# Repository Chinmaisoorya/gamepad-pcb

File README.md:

# Custom USB Gamepad PCB

A 2-layer PCB gamepad built around the ATmega32U4 microcontroller. It enumerates as a standard Xbox 360 controller on Windows via XInput — no drivers needed.

## Features

- Native USB 2.0 HID via ATmega32U4
- Dual analog joysticks (5-pin headers)
- 4 tactile buttons (A / B / X / Y)
- 16MHz external crystal for USB timing
- 2-layer PCB — hand-routed
- USB-C connector

## Preview

## Tech Stack

| Layer | Tool |
|-------|------|
| Schematic | KiCad 8 |
| PCB Layout | KiCad 8 |
| Firmware | Arduino + XInput library |
| Manufacturing | JLCPCB-compatible Gerbers |

## Repository Structure
gamepad-pcb/
├── hardware/ KiCad project + Gerbers
├── firmware/ Arduino XInput code
├── images/ Renders and screenshots
└── README.md

## Hardware Details

- **MCU:** ATmega32U4-AU (QFN-44)
- **Crystal:** 16MHz HC49
- **USB:** USB-C receptacle (USB 2.0)
- **Joysticks:** 5-pin headers × 2
- **Buttons:** 6mm tactile push buttons × 4
- **PCB:** 2-layer, 1.6mm FR4

## Building the Firmware

1. Install the [Arduino XInput library](https://github.com/dmadison/ArduinoXInput).
2. Open `firmware/gamepad.ino`.
3. Select **Arduino Leonardo** as the board (ATmega32U4).
4. Upload via USB.

The gamepad will appear in Windows as **"Xbox 360 Controller"**.

## Manufacturing

Gerbers are in `hardware/gamepad_gerbers.zip`. Upload directly to JLCPCB or PCBWay.

## License

MIT — free to use, modify, and build.

## Author

Chinmai soorya P — [www.linkedin.com/in/chinmai-soorya-p-52184941a]

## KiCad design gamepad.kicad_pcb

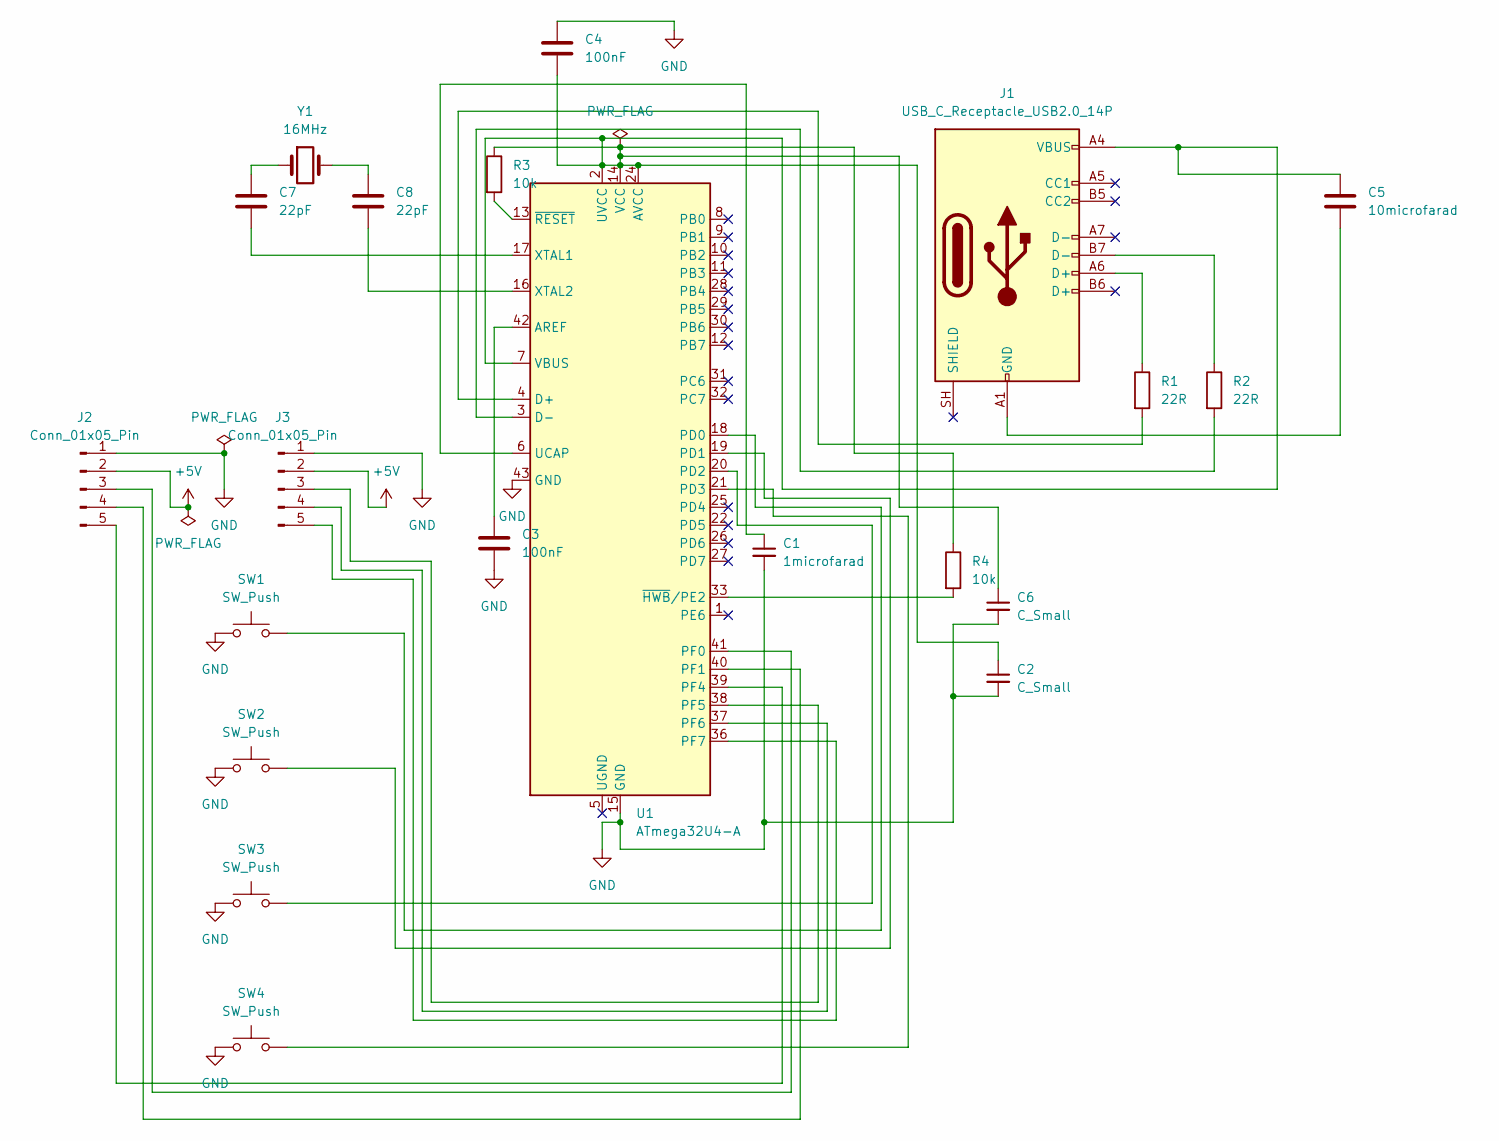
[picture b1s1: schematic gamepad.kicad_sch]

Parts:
C1: 1microfarad; C_0805_2012Metric
C2, C6: C_Small; C_0805_2012Metric
C3, C4: 100nF; C_0805_2012Metric
C5: 10microfarad; C_0805_2012Metric
C7, C8: 22pF; C_0805_2012Metric
J1: USB_C_Receptacle_USB2.0_14P; USB_C_Receptacle_HRO_TYPE-C-31-M-12
J2, J3: Conn_01x05_Pin; PinHeader_1x05_P2.54mm_Vertical
R1, R2: 22R; R_0805_2012Metric
R3, R4: 10k; R_0805_2012Metric
SW1, SW2, SW3, SW4: SW_Push; SW_PUSH_6mm_H5mm
U1: ATmega32U4-A; QFN-44-1EP_7x7mm_P0.5mm_EP5.2x5.2mm
Y1: 16MHz; Crystal_HC49-4H_Vertical

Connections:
+5V: J2.2, J3.2
GND: C1.2, C2.2, C3.2, C4.1, C6.2, J2.1, J3.1, SW1.1, SW2.1, SW3.1, SW4.1, U1.15 (GND), U1.43 (GND)
unnamed: C5.2, J1.A1 (GND), J1.A12 (GND), J1.B1 (GND), J1.B12 (GND)
unnamed: C7.1, Y1.1
unnamed: C8.1, Y1.2
unnamed: J1.A6 (D+), R1.1
unnamed: J1.B7 (D-), R2.1
unnamed: J2.3, U1.41 (PF0)
unnamed: J2.4, U1.40 (PF1)
unnamed: J2.5, U1.39 (PF4)
unnamed: J3.3, U1.38 (PF5)
unnamed: J3.4, U1.37 (PF6)
unnamed: J3.5, U1.36 (PF7)
unnamed: C3.1, U1.42 (AREF)
unnamed: R1.2, U1.4 (D+)
unnamed: R2.2, U1.3 (D-)
unnamed: SW1.2, U1.18 (PD0)
unnamed: SW2.2, U1.19 (PD1)
unnamed: SW3.2, U1.20 (PD2)
unnamed: SW4.2, U1.21 (PD3)
unnamed: C1.1, U1.6 (UCAP)
unnamed: C2.1, C4.2, C5.1, C6.1, J1.A4 (VBUS), J1.A9 (VBUS), J1.B4 (VBUS), J1.B9 (VBUS), R3.1, R4.1, U1.2 (UVCC), U1.7 (VBUS), U1.14 (VCC), U1.24 (AVCC), U1.34 (VCC), U1.44 (AVCC)
unnamed: C7.2, U1.17 (XTAL1)
unnamed: C8.2, U1.16 (XTAL2)
unnamed: R4.2, U1.33 (~HWB/PE2)
unnamed: R3.2, U1.13 (~RESET)

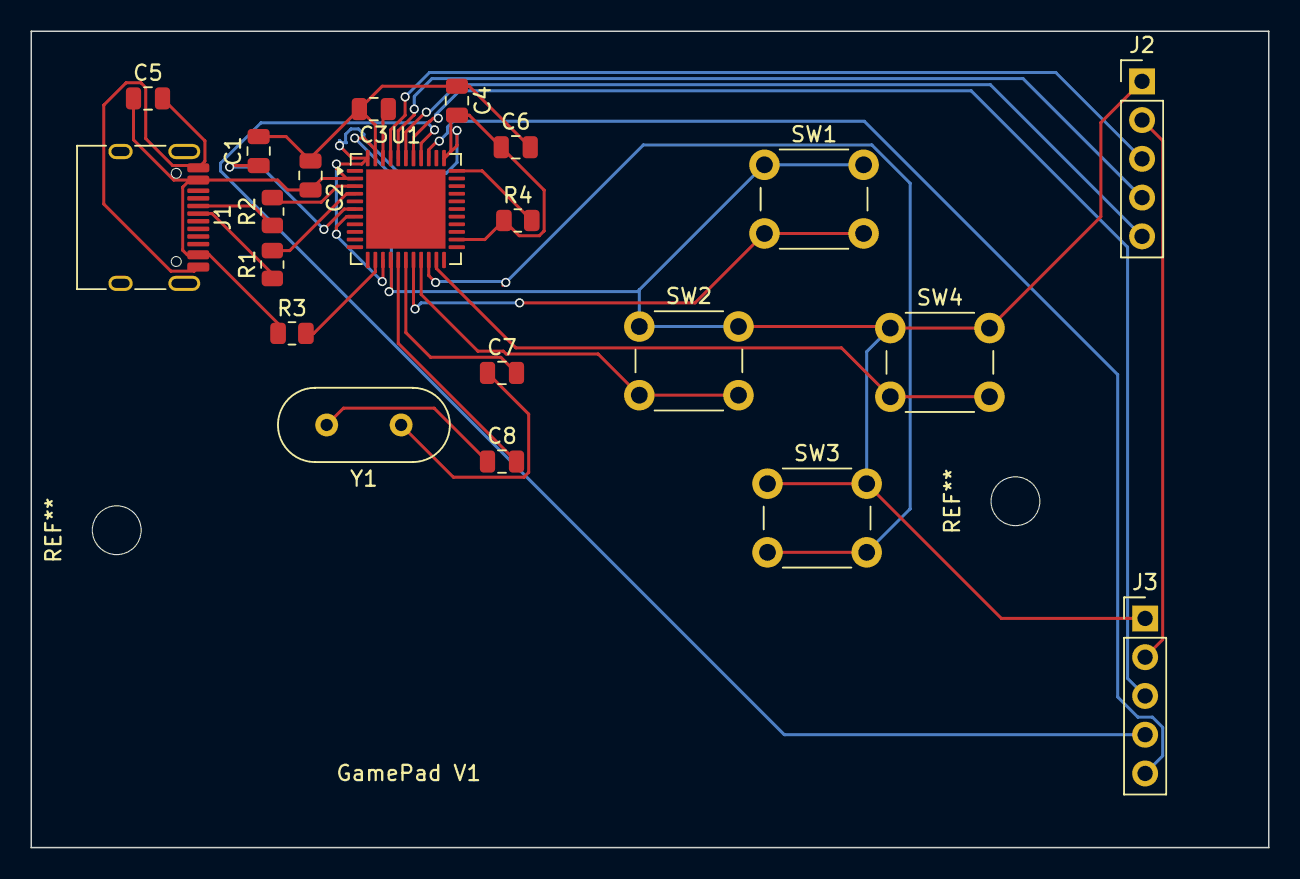
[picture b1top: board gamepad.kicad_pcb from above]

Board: 2 copper layers, 81.1 x 53.5 mm, 21 parts (0 on the bottom side), 26 nets.
